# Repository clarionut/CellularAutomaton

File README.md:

# Cellular Automaton

This repository contains details of an Arduino-based emulation of the [NonlinearCircuits Cellular Automata](https://www.nonlinearcircuits.com/modules/p/cellular-automata) synthesiser module but with additional functionality.

The original is a tour-de-force of 4xxx CMOS circuit design, but a microcontroller-based implementation is much simpler to design and assemble, probably cheaper and, most importantly, offers the possibility for interesting additional functionality. In particular, this implemetation allows a probabilistic approach to the cellular automaton rules and can run using its own internal clock.

The rules (more details in the Arduino code) determine if each cell will be OFF or allowed to be ON in the next generation. An OFF cell will definitely be OFF but an 'allowed' cell may be ON or OFF depending on a voltage controlled Survival probability. VC inputs of 5V (or above) will set the Survival pobability to 1 (and the cell will definitely be ON) while inputs of 0V (or below) give a survival probability nearer to 0 (and the cell will probably be OFF). Intermediate values give an increasing probability of survival as the control voltage increases. This has the effect of varying the density of ON cells in the grid and increasing the randomness of the grid patterns. The individual Seed cell inputs also accept analogue (0 - 5V) control voltages rather than simple gates allowing probabilistic seeding of the grid. There is also a global Seed probability control which can be set manually or by an external control voltage allowing the Cellular Automaton to be run without requiring direct inputs to the individual seed cells. The Seed probability inputs assign a probability of 0 for inputs of 0V or below, so the cellular automaton can be blanked.

In addition the module can run using an external clock or an internal clock with exponential voltage control. The clock mode is selected by a switch and the same input is used for both the external clock and voltage control of the internal clock.

Outputs are very similar to the Nonlinear Circuits original - a grid of 16 gate outputs (6V output in this case) which are high when the corresponding cell in the grid is ON and three pseudo-random CV outputs, one controlled by the top eight cells of the grid, one by the bottom eight cells and one by all cells combined.

## Hardware notes

The Arduino sketch requires 7 analogue inputs so I used a 16MHz Arduino Pro Mini board mounted on the PCB rather than an ATmega328P (only 6 analogue inputs) mounted directly on the board. This drives two CD4094B shift registers running on 6V which in turn drive the LED matrix and gate outputs. The 6V supply provides a normalled voltage to the probability and clock inputs via 10k resistors mounted on the input sockets; with the 50k input level potentiometers this provides 0 - 5V for each of the inputs in the absence of an external connection. Inputs are protected against out-of-range voltages. The LED matrix in the original is 3D printed and uses 16 green 3mm ultrabright LEDs. The STL files are on [Thingiverse](https://www.thingiverse.com/thing:6831147).

## KiCad files

The schematic and PCB files are provided in KiCad 7 format and as PDFs. Note that the front copper ground plane is excluded from the PDF for clarity but is present in the KiCad files. The schematic uses some custom symbols and the PCB some custom footprints, so you will need to download my [custom KiCad libraries](https://github.com/clarionut/kiCad_libraries) and tell KiCad where to find them. Note that Arduino Pro Minis don't all have the same footprint, so you may have to further customise the PCB. The PCB file is intended to be processed by the KiCad 'Round Tracks' plugin but will work perfectly well without. I've included the Gerber files but these will only be useful if you mount the PCB on brackets behind and perpendicular to the front panel.

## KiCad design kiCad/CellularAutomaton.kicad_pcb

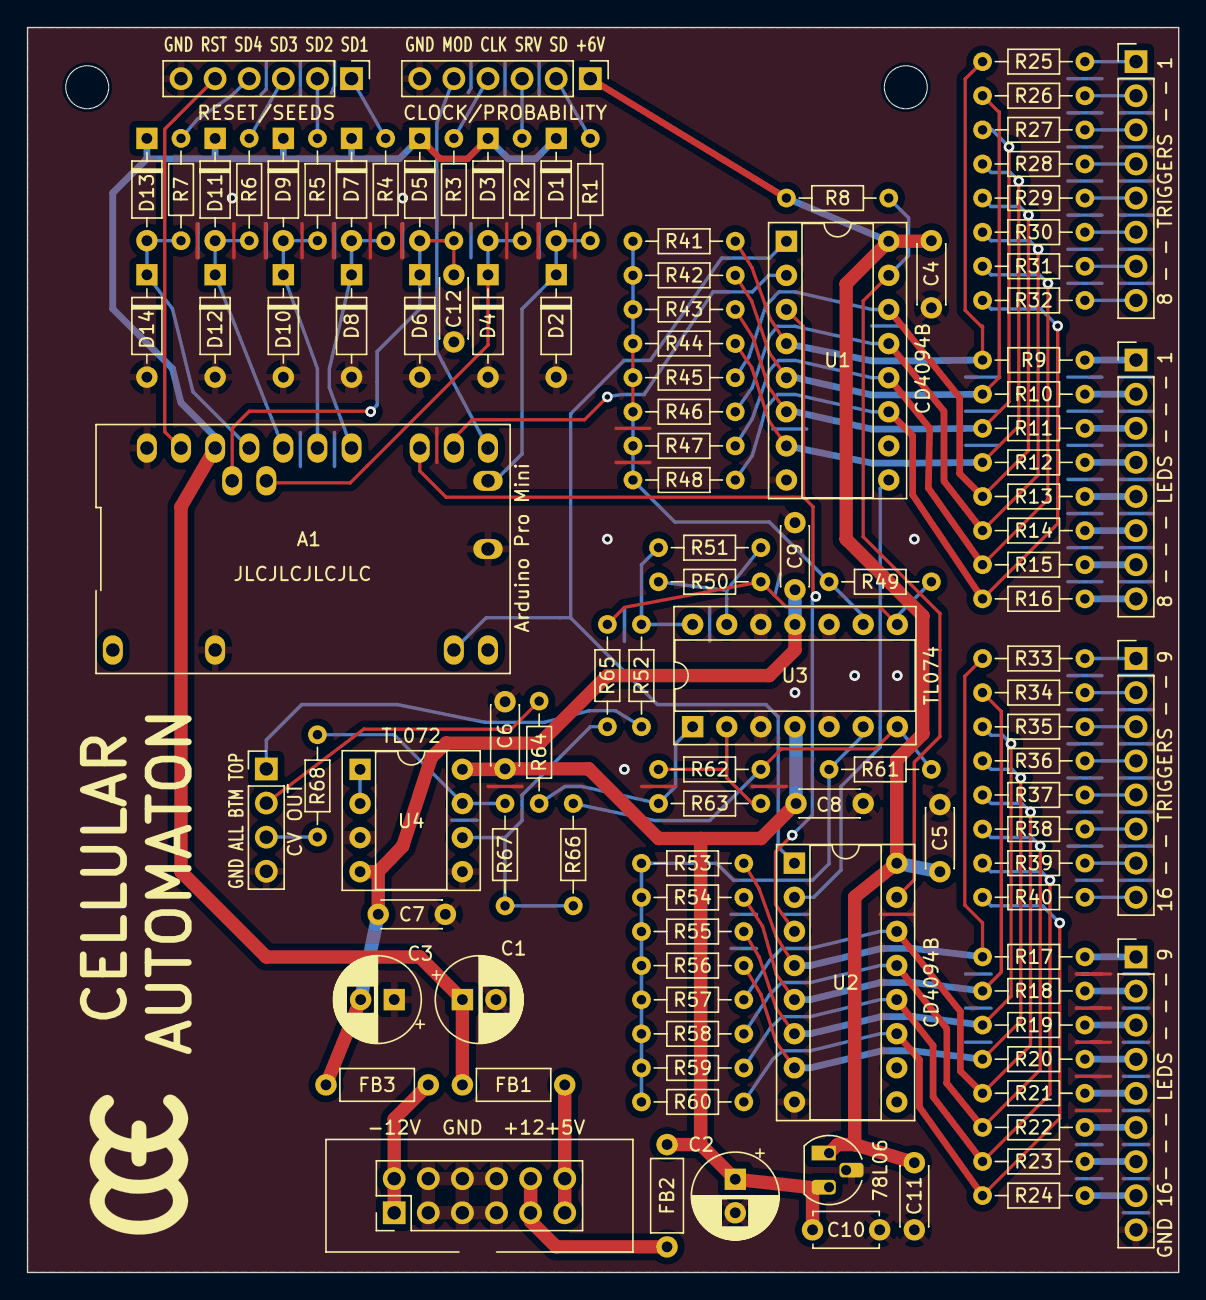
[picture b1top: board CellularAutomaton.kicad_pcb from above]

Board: 2 copper layers, 85.7 x 92.7 mm, 111 parts (0 on the bottom side), 91 nets.

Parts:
A1: Arduino_Pro_Mini
C1, C2, C3: 10u; CP_Radial_D6.3mm_P2.50mm
C4, C5, C6, C7, C8, C9, C11: 100n; C_Disc_D4.3mm_W1.9mm_P5.00mm
C10: 330n; C_Disc_D4.7mm_W2.5mm_P5.00mm
C12: 10n; C_Disc_D4.3mm_W1.9mm_P5.00mm
D1, D2, D3, D4, D5, D6, D7, D8, D9, D10, D11, D12, D13, D14: BAT43; D_DO-35_SOD27_P7.62mm_Horizontal
FB1, FB2, FB3: FB; L_Axial_L5.3mm_D2.2mm_P7.62mm_Horizontal_Vishay_IM-1
J9: PROB/CLOCK; PinHeader_1x06_P2.54mm_Vertical
J10: SEEDS/RST; PinHeader_1x06_P2.54mm_Vertical
J11: ROWS1&2; PinHeader_1x08_P2.54mm_Vertical
J12: ROWS3&4; PinHeader_1x09_P2.54mm_Vertical
J13: CV_OUT; PinHeader_1x04_P2.54mm_Vertical
J14: TRG1-8; PinHeader_1x08_P2.54mm_Vertical
J15: TRG9-16; PinHeader_1x08_P2.54mm_Vertical
J16: POWER; Power_2x06
R1, R2, R3, R4, R5, R6, R7, R8, R9, R10, R11, R12, R13, R14, R15, R16, R17, R18, R19, R20, R21, R22, R23, R24: 10k; R_Axial_DIN0204_L3.6mm_D1.6mm_P7.62mm_Horizontal
R25, R26, R27, R28, R29, R30, R31, R32, R33, R34, R35, R36, R37, R38, R39, R40: 2k2; R_Axial_DIN0204_L3.6mm_D1.6mm_P7.62mm_Horizontal
R41, R53: 1M; R_Axial_DIN0204_L3.6mm_D1.6mm_P7.62mm_Horizontal
R42, R54: 680k; R_Axial_DIN0204_L3.6mm_D1.6mm_P7.62mm_Horizontal
R43, R55: 470k; R_Axial_DIN0204_L3.6mm_D1.6mm_P7.62mm_Horizontal
R44, R56: 820k; R_Axial_DIN0204_L3.6mm_D1.6mm_P7.62mm_Horizontal
R45, R57: 330k; R_Axial_DIN0204_L3.6mm_D1.6mm_P7.62mm_Horizontal
R46, R50, R58, R62, R65, R66: 100k; R_Axial_DIN0204_L3.6mm_D1.6mm_P7.62mm_Horizontal
R47, R59: 150k; R_Axial_DIN0204_L3.6mm_D1.6mm_P7.62mm_Horizontal
R48, R60: 220k; R_Axial_DIN0204_L3.6mm_D1.6mm_P7.62mm_Horizontal
R49, R61: 47k; R_Axial_DIN0204_L3.6mm_D1.6mm_P7.62mm_Horizontal
R51, R63: 91k; R_Axial_DIN0204_L3.6mm_D1.6mm_P7.62mm_Horizontal
R52, R64, R68: 1k; R_Axial_DIN0204_L3.6mm_D1.6mm_P7.62mm_Horizontal
R67: 43k; R_Axial_DIN0204_L3.6mm_D1.6mm_P7.62mm_Horizontal
U1, U2: CD4094B; DIP-16_W7.62mm_Socket
U3: TL074; DIP-14_W7.62mm_Socket
U4: TL072; DIP-8_W7.62mm_Socket
U5: L78L06_TO92; TO-92_HandSolder

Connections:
+5V: A1.21 (VCC), C1.1, D1.1 (K), D3.1 (K), D5.1 (K), D7.1 (K), D9.1 (K), D11.1 (K), D13.1 (K), FB1.1
+6V: C4.1, C5.1, C11.2, J9.1, R8.1, U1.16 (Vdd), U2.16 (Vdd), U5.1 (VO)
+12V: C2.1, C6.1, C8.1, C10.2, FB2.1, U3.4 (V+), U4.8 (V+), U5.3 (VI)
-12V: C3.2, C7.1, C9.1, FB3.1, U3.11 (V-), U4.4 (V-)
/CLKMODE: A1.13 (D10), J9.5
/CLK/CV: J9.4, R3.1
/CLOCK: A1.15 (D12), U1.3 (Clock), U2.3 (Clock)
/CV_ALL: J13.3, R68.2
/CV_BTM: J13.2, R64.2
/CV_TOP: J13.1, R52.2
/DATA: A1.14 (D11), U1.2 (Data)
/L1: J11.1, R9.2
/L2: J11.2, R10.2
/L3: J11.3, R11.2
/L4: J11.4, R12.2
/L5: J11.5, R13.2
/L6: J11.6, R14.2
/L7: J11.7, R15.2
/L8: J11.8, R16.2
/L9: J12.1, R17.2
/L10: J12.2, R18.2
/L11: J12.3, R19.2
/L12: J12.4, R20.2
/L13: J12.5, R21.2
/L14: J12.6, R22.2
/L15: J12.7, R23.2
/L16: J12.8, R24.2
/OUT_EN: R8.2, U1.15 (Out_En), U2.15 (Out_En)
/QA1: R9.1, R25.1, R41.1, U1.4 (Q1)
/QA2: R10.1, R26.1, R42.1, U1.5 (Q2)
/QA3: R11.1, R27.1, R43.1, U1.6 (Q3)
/QA4: R12.1, R28.1, R44.1, U1.7 (Q4)
/QA5: R13.1, R29.1, R45.1, U1.14 (Q5)
/QA6: R14.1, R30.1, R46.1, U1.13 (Q6)
/QA7: R15.1, R31.1, R47.1, U1.12 (Q7)
/QA8: R16.1, R32.1, R48.1, U1.11 (Q8)
/QB1: R17.1, R33.1, R53.1, U2.4 (Q1)
/QB2: R18.1, R34.1, R54.1, U2.5 (Q2)
/QB3: R19.1, R35.1, R55.1, U2.6 (Q3)
/QB4: R20.1, R36.1, R56.1, U2.7 (Q4)
/QB5: R21.1, R37.1, R57.1, U2.14 (Q5)
/QB6: R22.1, R38.1, R58.1, U2.13 (Q6)
/QB7: R23.1, R39.1, R59.1, U2.12 (Q7)
/QB8: R24.1, R40.1, R60.1, U2.11 (Q8)
/RST: A1.22 (RST), J10.5
/SD1: J10.1, R4.1
/SD2: J10.2, R5.1
/SD3: J10.3, R6.1
/SD4: J10.4, R7.1
/SDPRB: J9.2, R1.1
/SRVPRB: J9.3, R2.1
/STROBE: A1.11 (D8), U1.1 (Strobe), U2.1 (Strobe)
/T1: J14.1, R25.2
/T2: J14.2, R26.2
/T3: J14.3, R27.2
/T4: J14.4, R28.2
/T5: J14.5, R29.2
/T6: J14.6, R30.2
/T7: J14.7, R31.2
/T8: J14.8, R32.2
/T9: J15.1, R33.2
/T10: J15.2, R34.2
/T11: J15.3, R35.2
/T12: J15.4, R36.2
/T13: J15.5, R37.2
/T14: J15.6, R38.2
/T15: J15.7, R39.2
/T16: J15.8, R40.2
GND: A1.4 (GND), A1.23 (GND), A1.29 (GND), C1.2, C2.2, C3.1, C4.2, C5.2, C6.2, C7.2, C8.2, C9.2, C10.1, C11.1, C12.1, D2.2 (A), D4.2 (A), D6.2 (A), D8.2 (A), D10.2 (A), D12.2 (A), D14.2 (A), J9.6, J10.6, J12.9, J13.4, J16.3, J16.4, J16.5, J16.6, J16.7, J16.8, U1.8 (Vss), U2.8 (Vss), U3.3 (+), U3.5 (+), U3.10 (+), U3.12 (+), U4.3 (+), U4.5 (+), U5.2 (GND)
unnamed: A1.17 (A0), D7.2 (A), D8.1 (K), R4.2
unnamed: A1.18 (A1), D9.2 (A), D10.1 (K), R5.2
unnamed: A1.19 (A2), D11.2 (A), D12.1 (K), R6.2
unnamed: A1.20 (A3), D13.2 (A), D14.1 (K), R7.2
unnamed: A1.26 (A4), D3.2 (A), D4.1 (K), R2.2
unnamed: A1.25 (A5), C12.2, D5.2 (A), D6.1 (K), R3.2
unnamed: A1.27 (A7), D1.2 (A), D2.1 (K), R1.2
unnamed: FB3.2, J16.1, J16.2
unnamed: FB2.2, J16.9, J16.10
unnamed: FB1.2, J16.11, J16.12
unnamed: R49.2, R50.1, R65.1, U3.8
unnamed: R51.2, R52.1, U3.14
unnamed: R61.2, R62.1, R66.1, U3.7
unnamed: R63.2, R64.1, U3.1
unnamed: R67.2, R68.1, U4.7
unnamed: U1.9 (Qs), U2.2 (Data)
unnamed: R62.2, R63.1, U3.2 (-)
unnamed: R53.2, R54.2, R55.2, R56.2, R57.2, R58.2, R59.2, R60.2, R61.1, U3.6 (-)
unnamed: R41.2, R42.2, R43.2, R44.2, R45.2, R46.2, R47.2, R48.2, R49.1, U3.9 (-)
unnamed: R50.2, R51.1, U3.13 (-)
unnamed: U4.1, U4.2 (-)
unnamed: R65.2, R66.2, R67.1, U4.6 (-)

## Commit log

2024-11-14 Update README.md
    An Arduino-based emulation of the Nonlinear Circuits Cellular Automata synth module with additional functionality
2024-11-14 Create temp
2024-11-14 Create KiCad
